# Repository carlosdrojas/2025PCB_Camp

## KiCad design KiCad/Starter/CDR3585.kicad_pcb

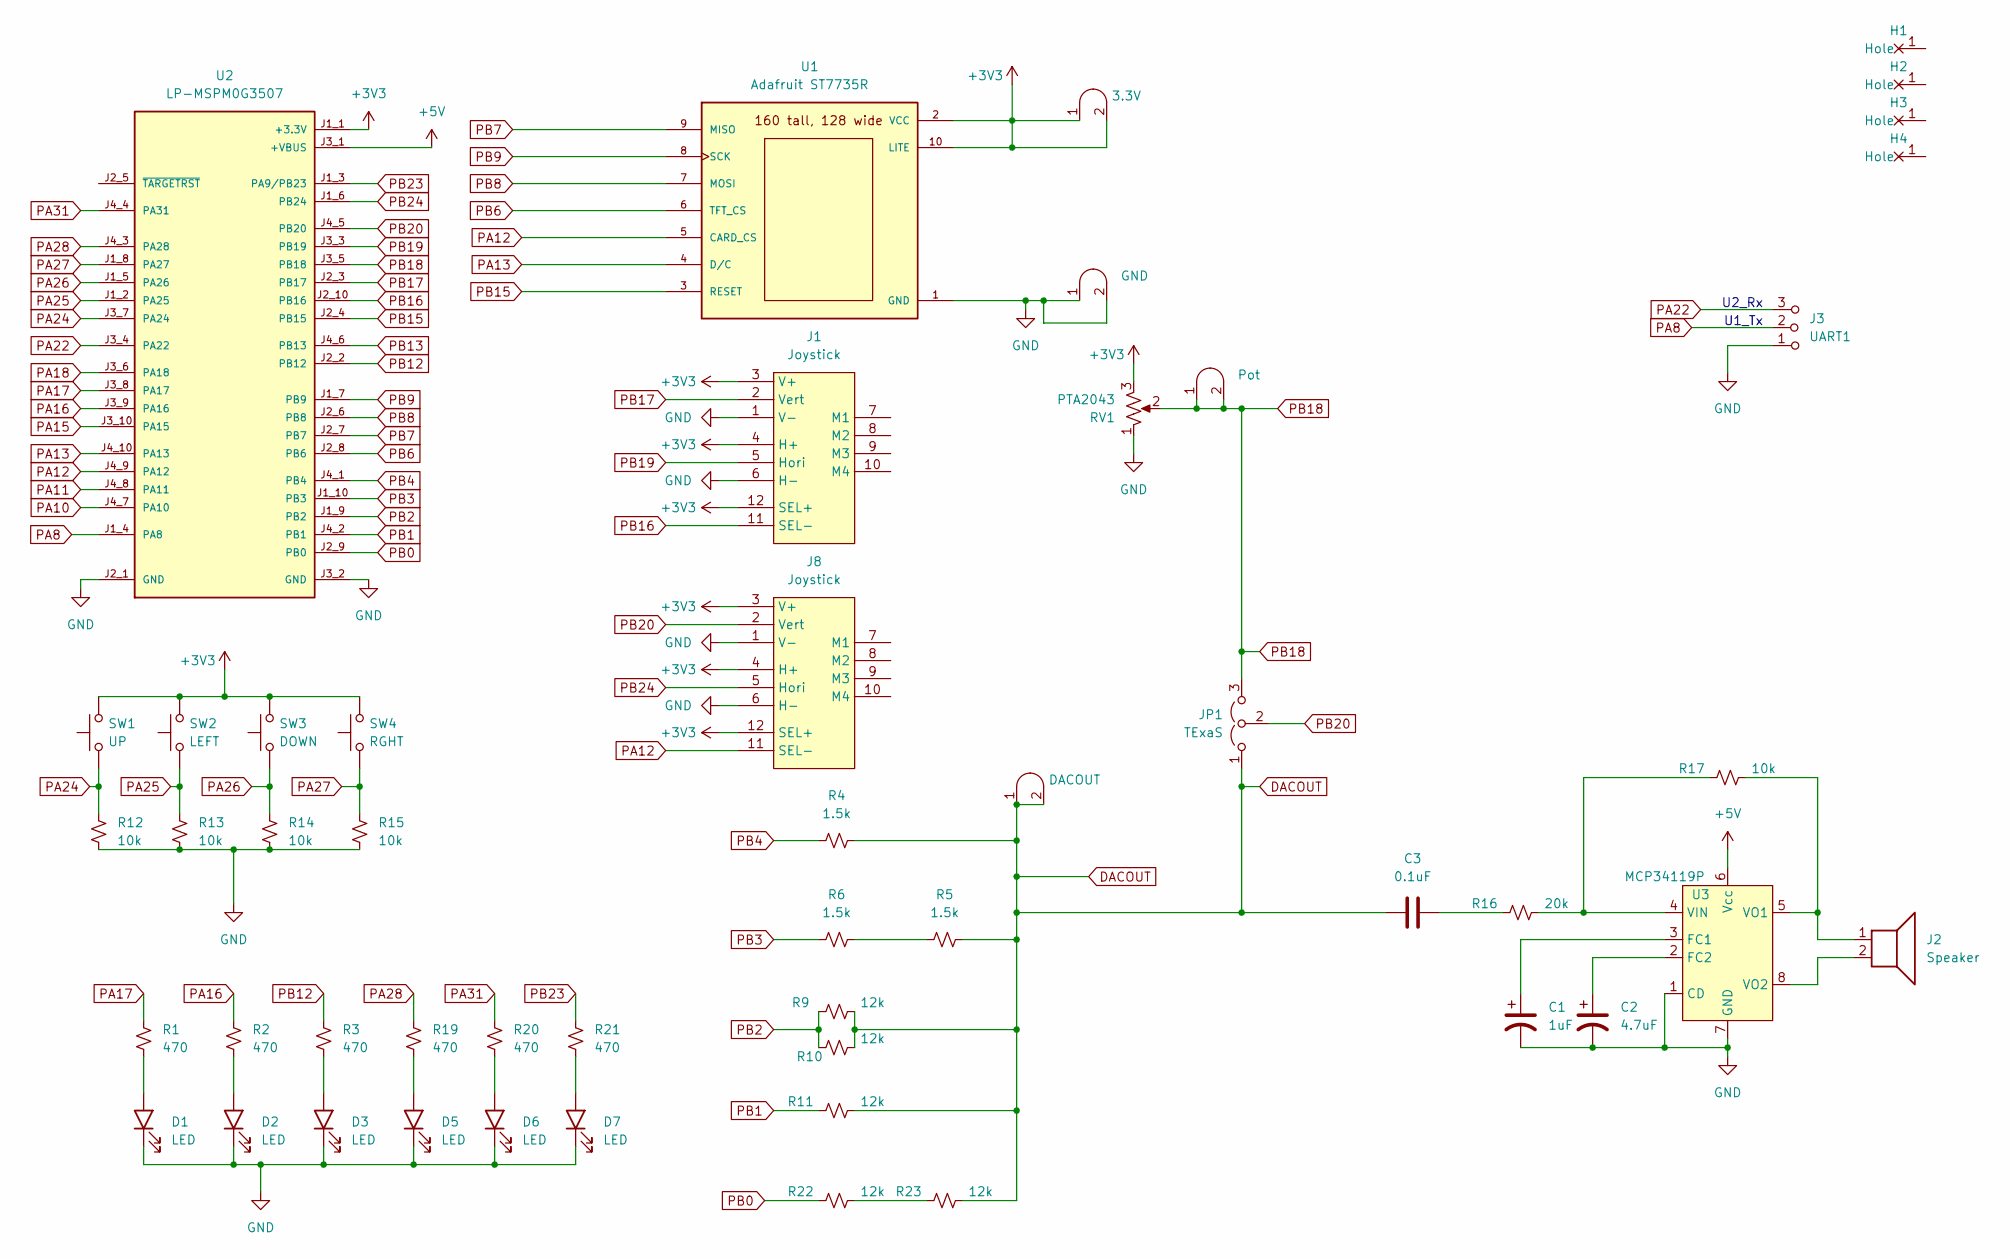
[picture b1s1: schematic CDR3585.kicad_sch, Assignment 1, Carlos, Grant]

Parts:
C1: 1uF; CP_Radial_Tantal200mil
C2: 4.7uF; CP_Radial_Tantal200mil
C3: 0.1uF; C_Axial_200mil
D1, D2, D3, D5, D6, D7: LED; LED_D5.0mm
H1, H2, H3, H4: MountingHole_4_40
J1, J8: Joystick; SparkfunJoystick
J2: Speaker; PinHeader_1x02_P2.54mm_Vertical
J3: UART1; PinHeader_1x03_P2.54mm_Vertical
J4: Pot; Testpoint_1x02_P2.54mm
J6: GND; Testpoint_1x02_P2.54mm
J7: DACOUT; Testpoint_1x02_P2.54mm
JP1: TExaS; PinHeader_1x03_P2.54mm_Vertical
R1, R2, R3, R19, R20, R21: 470; R_Axial_DIN0204_L3.6mm_D1.6mm_P7.62mm_Horizontal
R4, R5, R6: 1.5k; R_Axial_DIN0204_L3.6mm_D1.6mm_P7.62mm_Horizontal
R9, R10, R11, R22, R23: 12k; R_Axial_DIN0204_L3.6mm_D1.6mm_P7.62mm_Horizontal
R12, R13, R14, R15, R17: 10k; R_Axial_DIN0204_L3.6mm_D1.6mm_P7.62mm_Horizontal
R16: 20k; R_Axial_DIN0204_L3.6mm_D1.6mm_P7.62mm_Horizontal
RV1: PTA2043; PTA2043pot
SW1: UP; SW_PUSH_6mm
SW2: LEFT; SW_PUSH_6mm
SW3: DOWN; SW_PUSH_6mm
SW4: RGHT; SW_PUSH_6mm
TP1: 3.3V; Testpoint_1x02_P2.54mm
U1: Adafruit ST7735R; adafruit_st7735r
U2: LP-MSPM0G3507; ti_LP_MSPM0G3507
U3: MCP34119P; DIP-8_W7.62mm_LongPads

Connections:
+3V3: J1.3 (V+), J1.4 (H+), J1.12 (SEL+), J8.3 (V+), J8.4 (H+), J8.12 (SEL+), RV1.3, SW1.2, SW2.2, SW3.2, SW4.2, TP1.1 (A), TP1.2 (B), U1.2 (VCC), U1.10 (LITE), U2.J1_1 (+3.3V)
+5V: U2.J3_1 (+VBUS), U3.6 (Vcc)
DACOUT: C3.1, J7.1 (A), J7.2 (B), JP1.1 (A), R4.1, R5.1, R9.1, R10.1, R11.1, R23.1
GND: C1.2, C2.2, D1.1 (K), D2.1 (K), D3.1 (K), D5.1 (K), D6.1 (K), D7.1 (K), J1.1 (V-), J1.6 (H-), J3.1 (A), J6.1 (A), J6.2 (B), J8.1 (V-), J8.6 (H-), R12.2, R13.2, R14.2, R15.2, RV1.1, U1.1 (GND), U2.J2_1 (GND), U2.J3_2 (GND), U3.1 (CD), U3.7 (GND)
unnamed: C3.2, R16.2
unnamed: D1.2 (A), R1.2
unnamed: D2.2 (A), R2.2
unnamed: D3.2 (A), R3.2
unnamed: D5.2 (A), R19.2
unnamed: D6.2 (A), R20.2
unnamed: D7.2 (A), R21.2
unnamed: R5.2, R6.1
unnamed: R22.1, R23.2
unnamed: C1.1, U3.3 (FC1)
unnamed: C2.1, U3.2 (FC2)
unnamed: R16.1, R17.2, U3.4 (VIN)
unnamed: J2.1, R17.1, U3.5 (VO1)
unnamed: J2.2, U3.8 (VO2)
PA8: J3.2 (B), U2.J1_4 (PA8)
PA10: U2.J4_7 (PA10)
PA11: U2.J4_8 (PA11)
PA12: J8.11 (SEL-), U1.5 (CARD_CS), U2.J4_9 (PA12)
PA13: U1.4 (D/C), U2.J4_10 (PA13)
PA15: U2.J3_10 (PA15)
PA16: R2.1, U2.J3_9 (PA16)
PA17: R1.1, U2.J3_8 (PA17)
PA18: U2.J3_6 (PA18)
PA22: J3.3 (C), U2.J3_4 (PA22)
PA24: R12.1, SW1.1, U2.J3_7 (PA24)
PA25: R13.1, SW2.1, U2.J1_2 (PA25)
PA26: R14.1, SW3.1, U2.J1_5 (PA26)
PA27: R15.1, SW4.1, U2.J1_8 (PA27)
PA28: R19.1, U2.J4_3 (PA28)
PA31: R20.1, U2.J4_4 (PA31)
PB0: R22.2, U2.J2_9 (PB0)
PB1: R11.2, U2.J4_2 (PB1)
PB2: R9.2, R10.2, U2.J1_9 (PB2)
PB3: R6.2, U2.J1_10 (PB3)
PB4: R4.2, U2.J4_1 (PB4)
PB6: U1.6 (TFT_CS), U2.J2_8 (PB6)
PB7: U1.9 (MISO), U2.J2_7 (PB7)
PB8: U1.7 (MOSI), U2.J2_6 (PB8)
PB9: U1.8 (SCK), U2.J1_7 (PB9)
PB12: R3.1, U2.J2_2 (PB12)
PB13: U2.J4_6 (PB13)
PB15: U1.3 (RESET), U2.J2_4 (PB15)
PB16: J1.11 (SEL-), U2.J2_10 (PB16)
PB17: J1.2 (Vert), U2.J2_3 (PB17)
PB18: J4.1 (A), J4.2 (B), JP1.3 (B), RV1.2, U2.J3_5 (PB18)
PB19: J1.5 (Hori), U2.J3_3 (PB19)
PB20: J8.2 (Vert), JP1.2 (C), U2.J4_5 (PB20)
PB23: R21.1, U2.J1_3 (PA9/PB23)
PB24: J8.5 (Hori), U2.J1_6 (PB24)

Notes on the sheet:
U2_Rx
U1_Tx

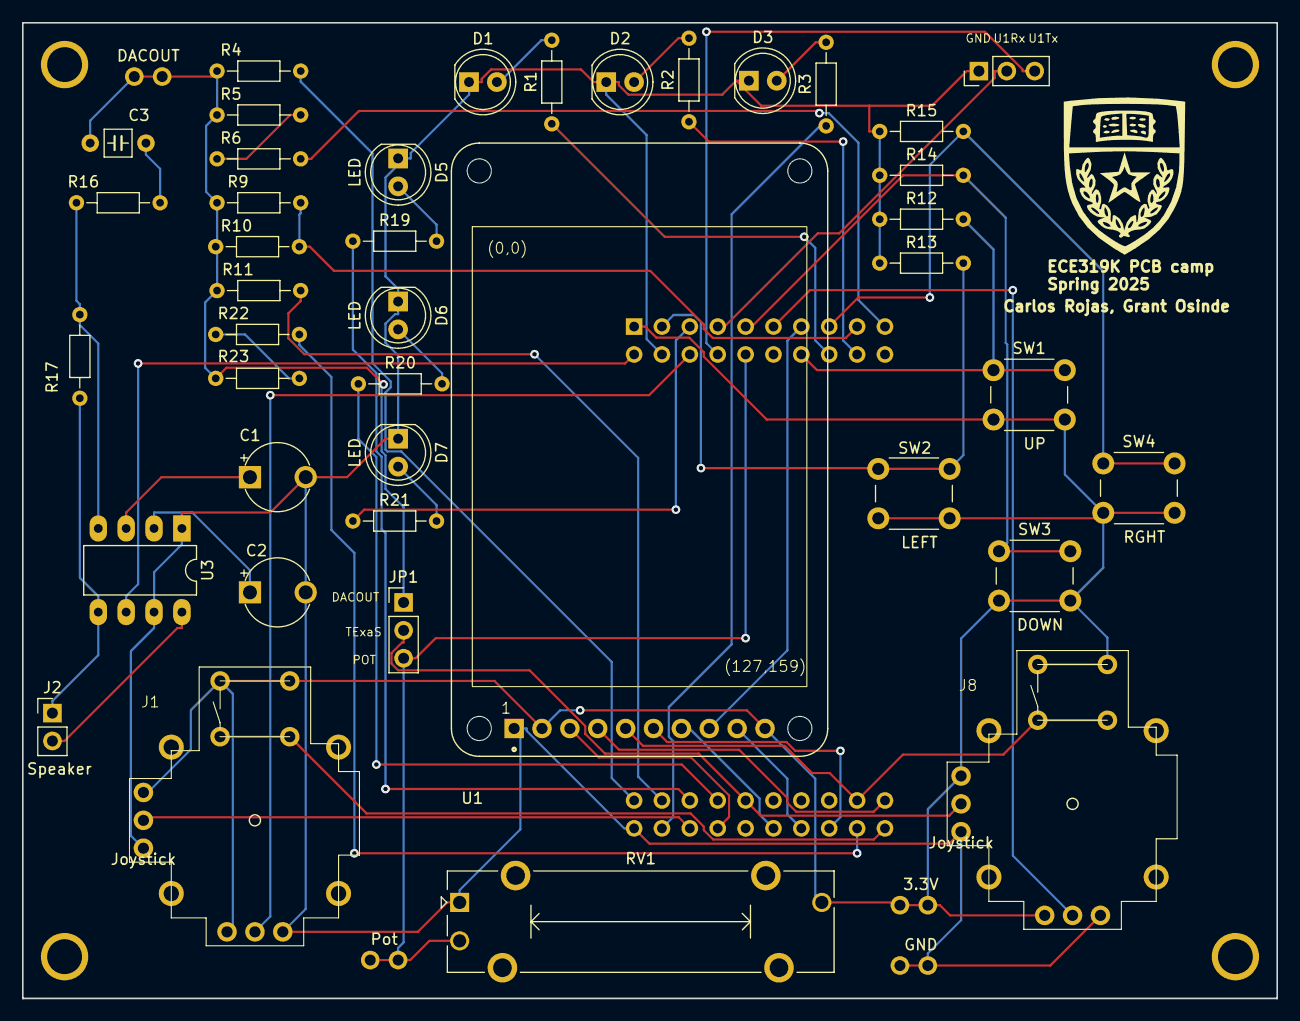
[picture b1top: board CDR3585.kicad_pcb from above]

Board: 2 copper layers, 114.3 x 88.9 mm, 50 parts (1 on the bottom side), 48 nets.

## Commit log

2025-03-19 loading starter folder
2025-03-24 project finsihed need review
